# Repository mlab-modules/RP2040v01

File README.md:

# RP2040v01 - RP2040 Processor Module
## Introduction

The [MLAB](https://www.mlab.cz/) module RP2040v01 featuring the [RP2040](https://www.raspberrypi.com/documentation/microcontrollers/rp2040.html) processor is a powerful and flexible development board designed for a wide range of applications. The [RP2040](https://www.raspberrypi.com/documentation/microcontrollers/rp2040.html), a microcontroller from the Raspberry Pi Foundation, offers dual Arm Cortex-M0+ cores and extensive peripheral support.

## Features

- **Processor**: Dual-core Arm Cortex-M0+ [RP2040](https://www.raspberrypi.com/documentation/microcontrollers/rp2040.html).
- **Buttons**: Boot and Reset buttons for easy programming and reset.
- **GPIO**: Processor pins are exposed on doubleheader pins for flexible connectivity, as is usual in MLAB modules.
- **LED**: An LED connected via a transistor on pin 25 for status indication.
- **USB**: USB-C connector for power and data communication.
- **Power Management**: Integrated power converter to step down from 5V to 3.3V.

## Processor Details

The RP2040 processor, developed by the Raspberry Pi Foundation, is a versatile microcontroller that includes the following key features:

- **Architecture**: Dual-core Arm Cortex-M0+.
- **Clock Speed**: Up to 133 MHz.
- **Memory**: 264KB of SRAM, and support for up to 16MB of external QSPI flash memory.
- **GPIO**: 30 GPIO pins, including a rich set of I/O options like UART, SPI, I2C, PWM, and ADC.
- **Timers**: Multiple timers and a real-time clock (RTC).
- **DMA**: Direct Memory Access controller for efficient data transfer.
- **Debugging**: SWD (Serial Wire Debug) interface for debugging and development.

## Module Schematic

The schematic of the RP2040v01 module illustrates the connections and components used in the design. This includes the layout of the RP2040 processor, power management circuitry, and GPIO pin headers.

If you would like more details, please consult the example codes and used ICs documentation.

## Programming Options

The RP2040 microcontroller offers multiple programming options, providing flexibility for various types of developers:

1. **MicroPython**:
   - An easy-to-use Python interpreter ideal for beginners.
   - Allows rapid prototyping and development with an extensive set of libraries.
   - [Official documentation](https://datasheets.raspberrypi.com/pico/raspberry-pi-pico-python-sdk.pdf)

2. **C/C++ with the Pico SDK**:
   - Provides low-level access to the hardware for maximum performance.
   - Suitable for more complex projects and experienced developers.
   - Requires setting up the Pico SDK and toolchain on your development environment.
   - [User-friendly documentation](https://datasheets.raspberrypi.com/pico/raspberry-pi-pico-c-sdk.pdf)

3. **Arduino IDE**:
   - Offers a familiar environment for those used to Arduino development.
   - Supports both the Mbed OS core and the C/C++ SDK-based core.
   - Simplifies the process of writing, compiling, and uploading sketches to the RP2040.
   - [Documentation](https://github.com/earlephilhower/arduino-pico)

### Drag-and-Drop Programming:
   - Allows you to upload firmware by simply dragging and dropping a UF2 file.
   - Useful for quick updates and easy deployment without needing an IDE.
   - Minimal knowledge required, best for beginners.

## Usage

1. **Flashing Firmware**:
   - Hold the Boot button and press the Reset button.
   - Release the Reset button while holding the Boot button to enter bootloader mode.
   - Drag and drop the firmware file onto the USB drive that appears.

2. **Programming**:
   - Select the appropriate board and port and use your preferred IDE (e.g., Thonny, VS Code, Arduino IDE).
   - Write your code and upload it to the RP2040.

## References
 - [RP2040 documentation page](https://www.raspberrypi.com/documentation/microcontrollers/rp2040.html)

## Examples

Example code and projects can be found in the `examples` directory of the repository. These include basic GPIO manipulation, sensor interfacing, and communication protocols.

## Applications

### Logic analyzer

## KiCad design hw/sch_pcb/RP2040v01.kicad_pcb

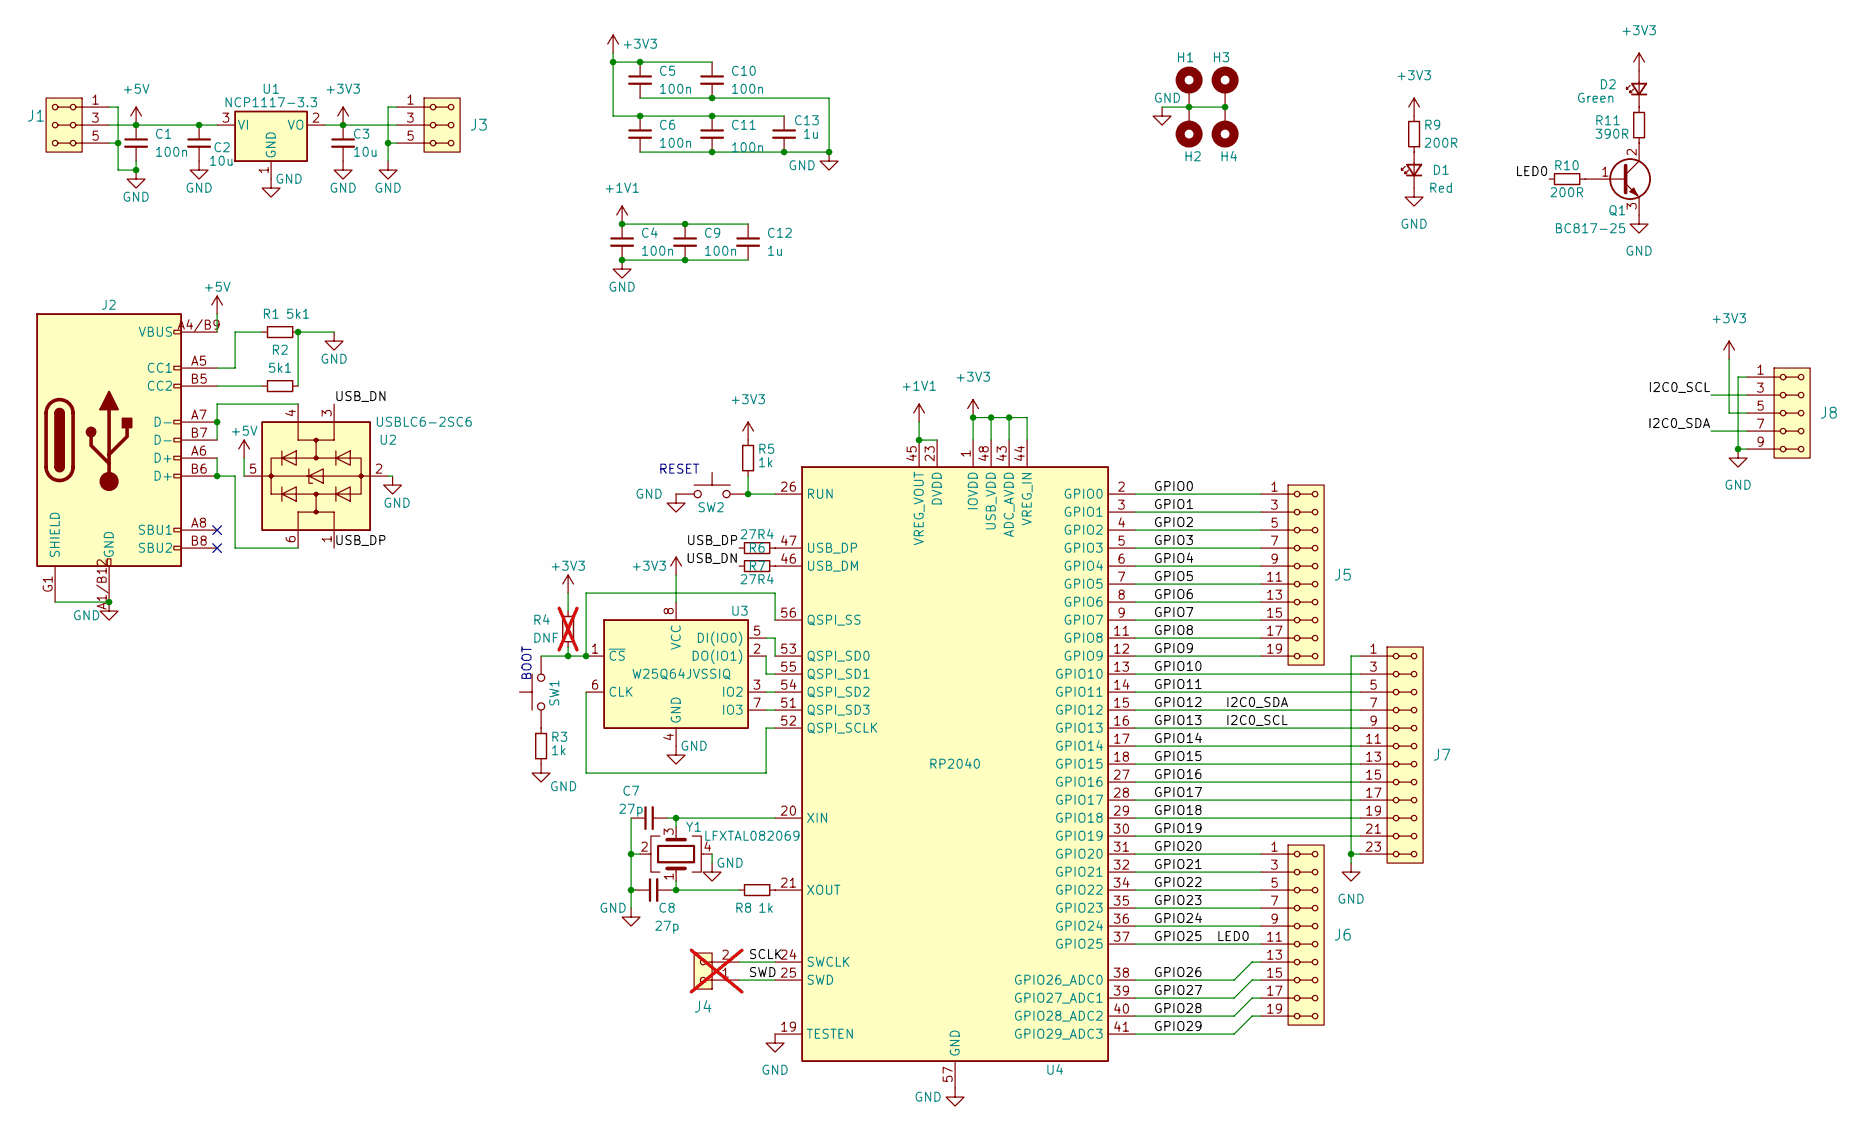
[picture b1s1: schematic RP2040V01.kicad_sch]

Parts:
C1, C4, C5, C6, C9, C10, C11: 100n; C_0805_2012Metric
C2, C3: 10u; C_0805_2012Metric
C7, C8: 27p; C_0805_2012Metric
C12, C13: 1u; C_0805_2012Metric
D1: Red; LED_1206_KPTR
D2: Green; LED_1206_KPTR
H1, H2, H3, H4: MountingHole_Pad; MountingHole_3.2mm_M3_Pad_Via
J1, J3: HEADER_1x03; Straight_2x03
J2: USBC_USB4105-GF-A; USBC GCT_USB4105-GF-A
J4: HEADER_1x10; Straight_1x02; not fitted
J5, J6: HEADER_1x10; Straight_2x10
J7: HEADER_1x10; Straight_2x12
J8: HEADER_2x05; Straight_2x05
Q1: BC817-25; SOT-23
R1, R2: 5k1; R_0805_2012Metric
R3, R5, R8: 1k; R_0805_2012Metric
R4: DNF; R_0805_2012Metric; not fitted
R6, R7: 27R4; R_0805_2012Metric
R9, R10: 200R; R_0805_2012Metric
R11: 390R; R_0805_2012Metric
SW1, SW2: 434133025816; SW_Push_1P1T_NO_Vertical_Wuerth_434133025816
U1: NCP1117-3.3; SOT-223-3_TabPin2
U2: USBLC6-2SC6; SOT-23-6
U3: W25Q64JVSSIQ; SOIC-8_5.23x5.23mm_P1.27mm
U4: RP2040; QFN-56-1EP_7x7mm_P0.4mm_EP3.2x3.2mm
Y1: LFXTAL082069; Crystal_SMD_SeikoEpson_FA238V-4Pin_3.2x2.5mm

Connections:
+1V1: C4.1, C9.1, C12.1, U4.23 (DVDD), U4.45 (VREG_VOUT), U4.50 (DVDD)
+3V3: C3.1, C5.1, C6.1, C10.1, C11.1, C13.1, D2.2 (A), J3.3, J3.4, J8.5, J8.6, R4.1, R5.1, R9.2, U1.2 (VO), U3.8 (VCC), U4.1 (IOVDD), U4.10 (IOVDD), U4.22 (IOVDD), U4.33 (IOVDD), U4.42 (IOVDD), U4.43 (ADC_AVDD), U4.44 (VREG_IN), U4.48 (USB_VDD), U4.49 (IOVDD)
+5V: C1.1, C2.1, J1.3, J1.4, J2.A4/B9 (VBUS), J2.B4/A9 (VBUS), U1.3 (VI), U2.5 (VBUS)
/GPIO0: J5.1, J5.2, U4.2 (GPIO0)
/GPIO1: J5.3, J5.4, U4.3 (GPIO1)
/GPIO2: J5.5, J5.6, U4.4 (GPIO2)
/GPIO3: J5.7, J5.8, U4.5 (GPIO3)
/GPIO4: J5.9, J5.10, U4.6 (GPIO4)
/GPIO5: J5.11, J5.12, U4.7 (GPIO5)
/GPIO6: J5.13, J5.14, U4.8 (GPIO6)
/GPIO7: J5.15, J5.16, U4.9 (GPIO7)
/GPIO8: J5.17, J5.18, U4.11 (GPIO8)
/GPIO9: J5.19, J5.20, U4.12 (GPIO9)
/GPIO10: J7.3, J7.4, U4.13 (GPIO10)
/GPIO11: J7.5, J7.6, U4.14 (GPIO11)
/GPIO12: J7.7, J7.8, J8.7, J8.8, U4.15 (GPIO12)
/GPIO13: J7.9, J7.10, J8.3, J8.4, U4.16 (GPIO13)
/GPIO14: J7.11, J7.12, U4.17 (GPIO14)
/GPIO15: J7.13, J7.14, U4.18 (GPIO15)
/GPIO16: J7.15, J7.16, U4.27 (GPIO16)
/GPIO17: J7.17, J7.18, U4.28 (GPIO17)
/GPIO18: J7.19, J7.20, U4.29 (GPIO18)
/GPIO19: J7.21, J7.22, U4.30 (GPIO19)
/GPIO20: J6.1, J6.2, U4.31 (GPIO20)
/GPIO21: J6.3, J6.4, U4.32 (GPIO21)
/GPIO22: J6.5, J6.6, U4.34 (GPIO22)
/GPIO23: J6.7, J6.8, U4.35 (GPIO23)
/GPIO24: J6.9, J6.10, U4.36 (GPIO24)
/GPIO25: J6.11, J6.12, R10.1, U4.37 (GPIO25)
/GPIO26: J6.13, J6.14, U4.38 (GPIO26_ADC0)
/GPIO27: J6.15, J6.16, U4.39 (GPIO27_ADC1)
/GPIO28: J6.17, J6.18, U4.40 (GPIO28_ADC2)
/GPIO29: J6.19, J6.20, U4.41 (GPIO29_ADC3)
/SCLK: J4.2, U4.24 (SWCLK)
/SWD: J4.1, U4.25 (SWD)
/USB_DN: R7.1, U2.3 (I/O2)
/USB_DP: R6.1, U2.1 (I/O1)
GND: C1.2, C2.2, C3.2, C4.2, C5.2, C6.2, C7.1, C8.1, C9.2, C10.2, C11.2, C12.2, C13.2, D1.1 (K), H1.1, H2.1, H3.1, H4.1, J1.1, J1.2, J1.5, J1.6, J2.A1/B12 (GND), J2.B1/A12 (GND), J2.G1 (SHIELD), J2.G2 (SHIELD), J2.G3 (SHIELD), J2.G4 (SHIELD), J3.1, J3.2, J3.5, J3.6, J7.1, J7.2, J7.23, J7.24, J8.1, J8.2, J8.9, J8.10, Q1.3 (E), R1.2, R2.2, R3.2, SW2.1, U1.1 (GND), U2.2 (GND), U3.4 (GND), U4.19 (TESTEN), U4.57 (GND), Y1.2, Y1.4
unnamed: C8.2, R8.2, Y1.1
unnamed: D1.2 (A), R9.1
unnamed: D2.1 (K), R11.1
unnamed: J2.A5 (CC1), R1.1
unnamed: J2.B5 (CC2), R2.1
unnamed: J2.A6 (D+), J2.B6 (D+), U2.6 (I/O1)
unnamed: J2.A7 (D-), J2.B7 (D-), U2.4 (I/O2)
unnamed: Q1.1 (B), R10.2
unnamed: Q1.2 (C), R11.2
unnamed: R3.1, SW1.1
unnamed: U3.6 (CLK), U4.52 (QSPI_SCLK)
unnamed: U3.5 (DI(IO0)), U4.53 (QSPI_SD0)
unnamed: U3.2 (DO(IO1)), U4.55 (QSPI_SD1)
unnamed: U3.3 (IO2), U4.54 (QSPI_SD2)
unnamed: U3.7 (IO3), U4.51 (QSPI_SD3)
unnamed: R4.2, SW1.2, U3.1 (~CS), U4.56 (QSPI_SS)
unnamed: R5.2, SW2.2, U4.26 (RUN)
unnamed: R7.2, U4.46 (USB_DM)
unnamed: R6.2, U4.47 (USB_DP)
unnamed: C7.2, U4.20 (XIN), Y1.3
unnamed: R8.1, U4.21 (XOUT)

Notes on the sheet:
BOOT
RESET

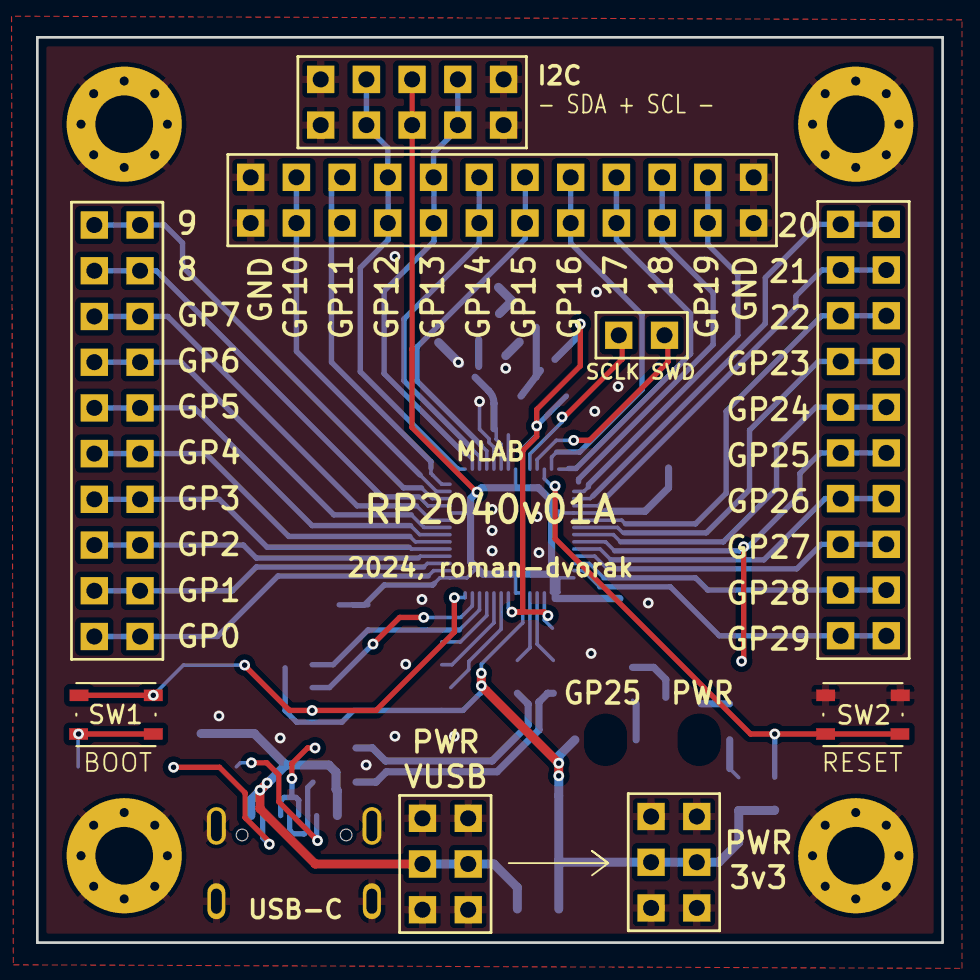
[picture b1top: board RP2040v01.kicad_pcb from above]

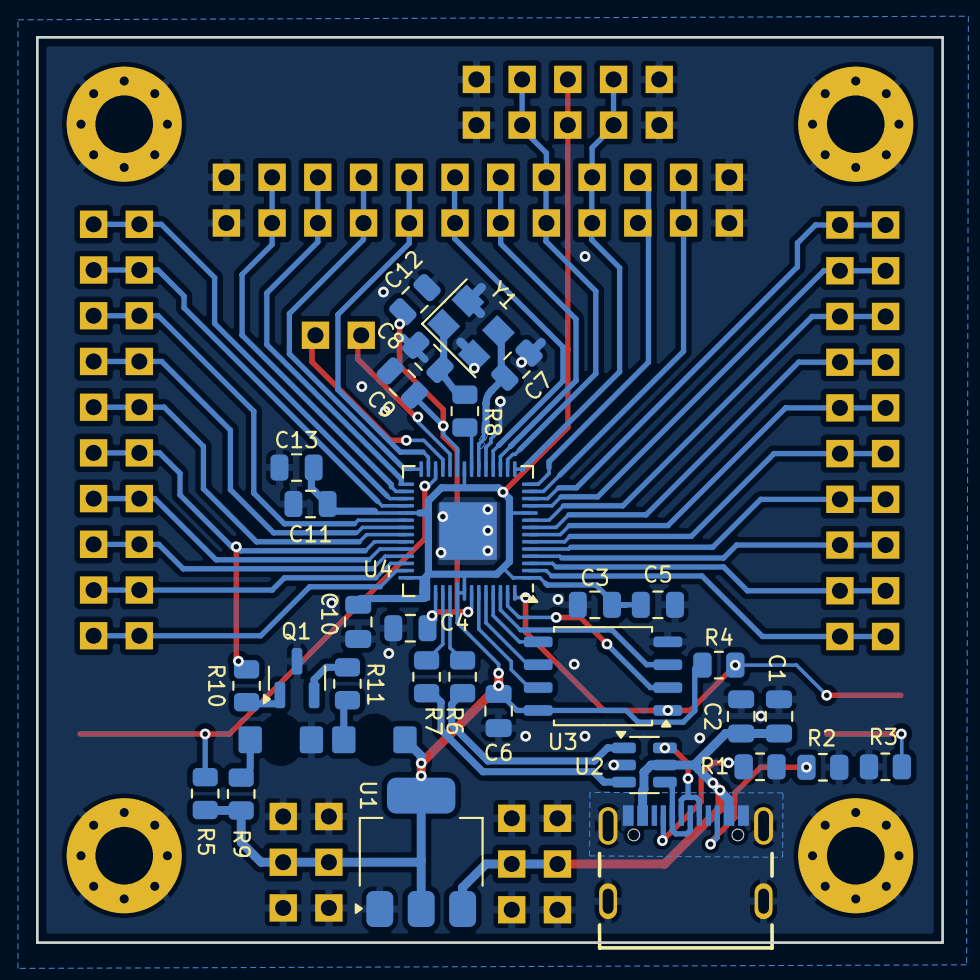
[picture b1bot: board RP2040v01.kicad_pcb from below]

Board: 2 copper layers, 50.3 x 50.3 mm, 46 parts (33 on the bottom side), 59 nets.

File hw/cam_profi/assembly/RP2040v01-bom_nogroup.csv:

Component,Description,Part,References,Value,Footprint,Quantity Per PCB,Datasheet,obchod
1,"Unpolarized capacitor, small symbol",C_Small,C7C8,27p,C_0805_2012Metric,2,~,TME
2,"Unpolarized capacitor, small symbol",C_Small,C1C4C5C6C9C10C11,100n,C_0805_2012Metric,7,~,TME
3,"Unpolarized capacitor, small symbol",C_Small,C12C13,1u,C_0805_2012Metric,2,~,TME
4,"Unpolarized capacitor, small symbol",C_Small,C2C3,10u,C_0805_2012Metric,2,~,TME
5,"Light emitting diode, small symbol",LED_Small,D2,Green,LED_1206_KPTR,1,~,OK
6,"Light emitting diode, small symbol",LED_Small,D1,Red,LED_1206_KPTR,1,~,OK
7,"2x03 2.54 mm pitch header, 2 pins next to each other are connected",HEADER_2x03_PARALLEL,J1J3,HEADER_1x03,Straight_2x03,2,,
8,"2x10 2.54 mm pitch header, 2 pins next to each other are connected",HEADER_2x10_PARALLEL,J5J6,HEADER_1x10,Straight_2x10,2,,
9,"2x12 2.54 mm pitch header, 2 pins next to each other are connected",HEADER_2x12_PARALLEL,J7,HEADER_1x10,Straight_2x12,1,,
10,"2x05 2.54 mm pitch header, 2 pins next to each other are connected",HEADER_2x05_PARALLEL,J8,HEADER_2x05,Straight_2x05,1,,
11,USB 2.0-only Type-C Receptacle connector,USBC_USB4105-GF-A,J2,USBC_USB4105-GF-A,USBC GCT_USB4105-GF-A,1,https://www.usb.org/sites/default/files/documents/usb_type-c.zip,OK
12,"NPN transistor, base/collector/emitter",Q_NPN_BCE,Q1,BC817-25,SOT-23,1,~,TME
13,"Resistor, small symbol",R_Small,R6R7,27R4,R_0805_2012Metric,2,~,TME
14,"Resistor, small symbol",R_Small,R9R10,200R,R_0805_2012Metric,2,~,TME
15,"Resistor, small symbol",R_Small,R11,390R,R_0805_2012Metric,1,~,
16,"Resistor, small symbol",R_Small,R3R5R8,1k,R_0805_2012Metric,3,~,TME
17,"Resistor, small symbol",R_Small,R1R2,5k1,R_0805_2012Metric,2,~,TME
18,"Push button switch, generic, two pins",SW_Push,SW1SW2,434133025816,SW_Push_1P1T_NO_Vertical_Wuerth_434133025816,2,~,TME
19,"1A Low drop-out regulator, Fixed Output 3.3V, SOT-223",NCP1117-3.3_SOT223,U1,NCP1117-3.3,SOT-223-3_TabPin2,1,http://www.onsemi.com/pub_link/Collateral/NCP1117-D.PDF,TME
20,A microcontroller by Raspberry Pi,RP2040,U4,RP2040,QFN-56-1EP_7x7mm_P0.4mm_EP3.2x3.2mm,1,https://datasheets.raspberrypi.com/rp2040/rp2040-datasheet.pdf,Farnell
21,"Very low capacitance ESD protection diode, 2 data-line, SOT-23-6",USBLC6-2SC6,U2,USBLC6-2SC6,SOT-23-6,1,https://www.st.com/resource/en/datasheet/usblc6-2.pdf,TME
22,"128Mb Serial Flash Memory, Standard/Dual/Quad SPI, SOIC-8",W25Q128JVS,U3,W25Q64JVSSIQ,SOIC-8_5.23x5.23mm_P1.27mm,1,http://www.winbond.com/resource-files/w25q128jv_dtr%20revc%2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,Mouser
23,"Four pin crystal, GND on pins 2 and 4",Crystal_GND24,Y1,LFXTAL082069,Crystal_SMD_SeikoEpson_FA238V-4Pin_3.2x2.5mm,1,~,Farnell

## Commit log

2024-06-03 add actions
2024-06-03 readme
2024-06-03 Update metadata files
2024-06-03 rename files
2024-06-03 Update actions products
2024-06-06 Change path to title block.
2024-06-09 Update metadata.yaml
    Select the specific title image.
2024-06-09 Fix bottom silkscreen.
2024-07-08 Create placeholder
2024-07-08 Update tindie.md
    synchronize with tindie.
2024-07-15 Update workflow files
2026-02-22 Update project to KiCADv9.
2026-02-22 Automatic update of KiCAD outputs
2026-03-11 Cleanup Fab layer.
